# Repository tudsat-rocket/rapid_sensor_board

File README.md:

# Rapid Sensor Board
this module is meant to be a general-purpose amplifier which is going to be used for all analogue sensors which will be in the rocket, those include the WIKA pressure sensors as well as the fancy-fins strain gauges.

## Description
The main function of the module is to amplify signals with low voltage levels that are too small to be useful for our ADCs. Therefore the board has two sides with solder pads, one to connect to the IO board and one to connect to a sensor. The layout is designed in a way, that the sensor side is compatible with the WIKA TPR-Flex PCBs.

## Features
* Selectable gain (1-1000) -> the selection of RG1 will determine the gain (G = 1 + 49,4kOhm/RG)
* selectable offset -> output offset can either be 0V or Vcc/2
* Breakaway mounting holes
## Connections
### To IO-Board:
Connects the amplifier module with the IO-Board with the following pins:
* u+  ->  positive supply voltage (3-36V)
* u-  ->  gnd as "neg" supply voltage (only use in single supply mode) | reference for the output signal.
* o+  ->  amplified signal, references gnd (u-)
* ref  ->  selected reference signal (0V or Vcc/2) can be used to get additional information (e.g. detect noise on supply line(?))

### To sensor:
Connects the amplifier module with the Sensor with the following pins:
* u+  -> positive supply voltage (filtered supply voltage)
* u-  -> neg. supply voltage (gnd)
* s+  -> positive signal
* s-  -> negative signal

## User guideline:
The Gain resistor (RG1) must be chosen in a way that the expected maximum amplified voltage is lower than 4.85V (5V - 0.15V) and the expected minimum amplified voltage is higher than 0.1V if a smaller (or negative) output voltage is expected the solder jumper for the reference voltage needs to be connected to 3 to set an output shift.
Only if the connected sensor is expected to output a signal which exclusively results in an output signal that is in the above given values, can the reference solder jumper be set to 1.

The above-given adjustments are necessary as the IO module is only able to read values between 0V and 5V. A higher Input voltage can be used if the connected sensor needs a supply voltage which exceeds 5V. The amplified signal then still needs to be smaller than the given 4.85V.

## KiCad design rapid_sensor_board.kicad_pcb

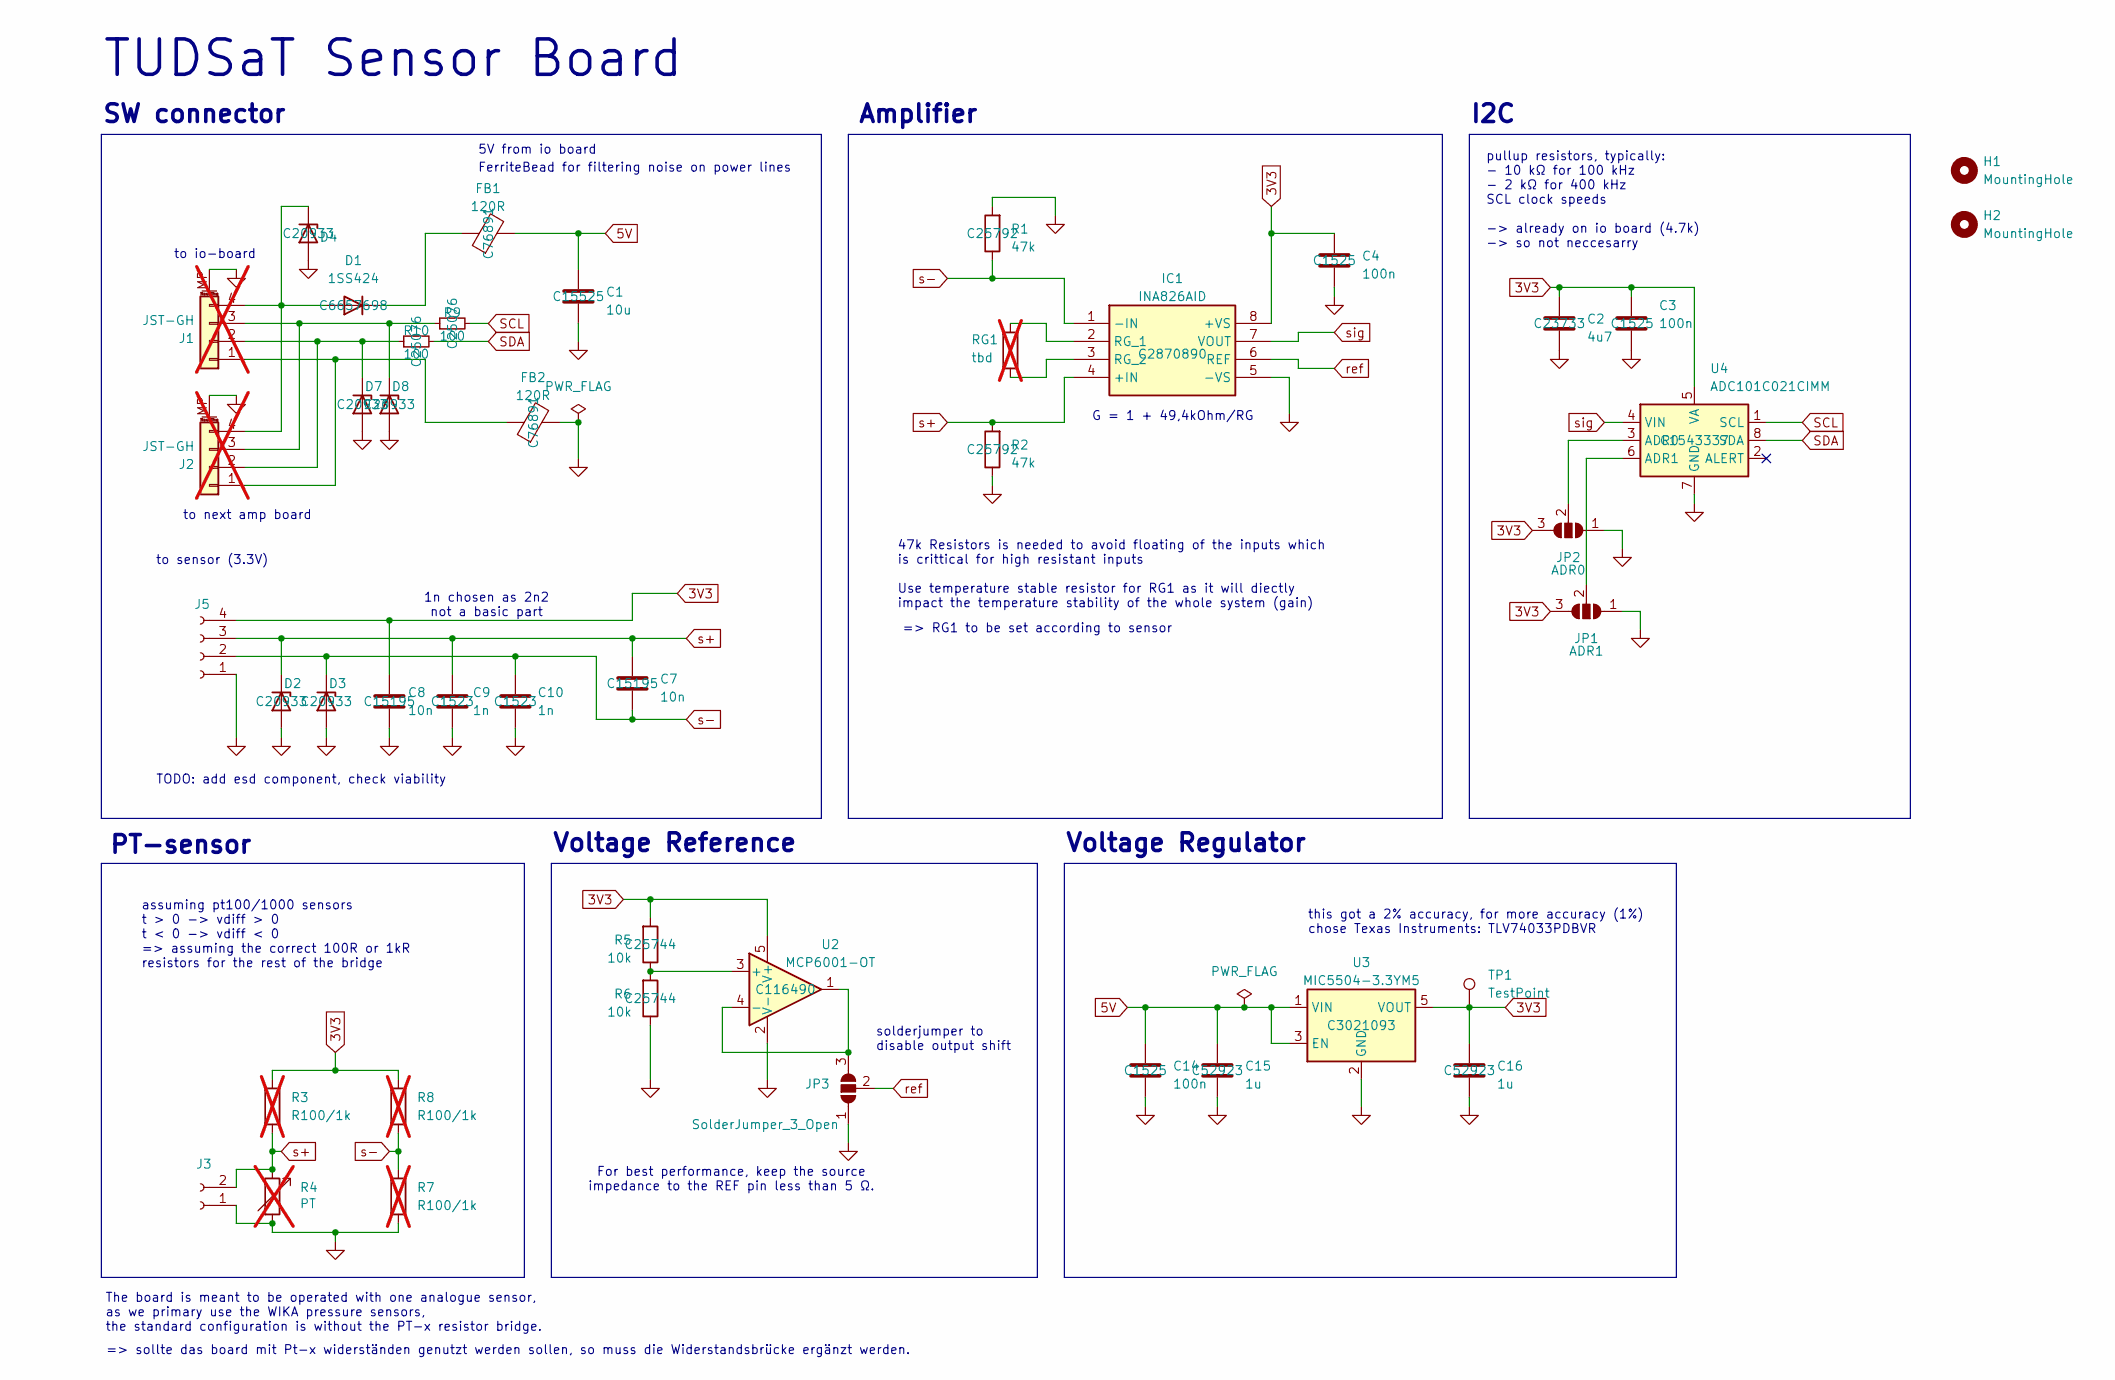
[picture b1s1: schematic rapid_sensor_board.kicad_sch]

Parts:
C1: 10u; C_0402_1005Metric; LCSC C15525
C2: 4u7; C_0402_1005Metric; LCSC C23733
C3, C4, C14: 100n; C_0402_1005Metric; LCSC C1525
C7, C8: 10n; C_0402_1005Metric; LCSC C15195
C9, C10: 1n; C_0402_1005Metric; LCSC C1523
C15, C16: 1u; C_0402_1005Metric; LCSC C52923
D1: 1SS424; D_SOD-523; LCSC C6657698
D2, D3, D7, D8: ESD5Z36; D_SOD-523; LCSC C20933
D4: ESD5Zxx; D_SOD-523; LCSC C20933
FB1, FB2: 120R; L_0402_1005Metric; LCSC C76891
H1, H2: MountingHole; MountingHole_2.2mm_M2_DIN965_Pad
IC1: INA826AID; WSON-8-1EP_3x3mm_P0.5mm_EP1.2x2mm; Mouser Part Number 595-INA826AID
J1, J2: JST-GH; JST_GH_SM04B-GHS-TB_1x04-1MP_P1.25mm_Horizontal; Part# BM04B-GHS-TBT; LCSC C161692; not fitted
J3: Conn_01x02_Socket; R_Axial_DIN0204_L3.6mm_D1.6mm_P1.90mm_Vertical
J5: Conn_01x04_Socket; PinHeader_1x04_P1.27mm_Vertical
JP1: ADR1; SolderJumper-3_P1.3mm_Open_RoundedPad1.0x1.5mm
JP2: ADR0; SolderJumper-3_P1.3mm_Open_RoundedPad1.0x1.5mm
JP3: SolderJumper_3_Open; SolderJumper-3_P1.3mm_Open_Pad1.0x1.5mm
R1: 47k; R_0402_1005Metric; LCSC C25792
R2: 47k; R_0402_1005Metric_Pad0.72x0.64mm_HandSolder; LCSC C25792
R3, R7, R8: R100/1k; R_0805_2012Metric_Pad1.20x1.40mm_HandSolder; not fitted
R4: PT; not fitted
R5, R6: 10k; R_0402_1005Metric_Pad0.72x0.64mm_HandSolder; LCSC C25744
R9, R10: 100; R_0402_1005Metric; LCSC C25076
RG1: tbd; R_1206_3216Metric_Pad1.30x1.75mm_HandSolder; not fitted
TP1: TestPoint; TestPoint_Pad_D1.5mm
U2: MCP6001-OT; SOT-23-5; LCSC C116490
U3: MIC5504-3.3YM5; SOT-23-5; LCSC C3021093
U4: ADC101C021CIMM; VSSOP-8_3x3mm_P0.65mm; LCSC C1543337

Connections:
3V3: C2.1, C3.1, C4.1, C8.1, C16.1, IC1.8 (+VS), J5.4, JP1.3 (B), JP2.3 (B), R3.1, R5.2, R8.1, TP1.1, U2.5 (V+), U3.5 (VOUT), U4.5 (VA)
5V: C1.1, C14.1, C15.1, FB1.2, U3.1 (VIN), U3.3 (EN)
GND: C1.2, C2.2, C3.2, C4.2, C8.2, C9.2, C10.2, C14.2, C15.2, C16.2, D2.2 (A), D3.2 (A), D4.2 (A), D7.2 (A), D8.2 (A), FB2.2, IC1.5 (-VS), J1.MP (MountPin), J2.MP (MountPin), J3.1, J5.1, JP1.1 (A), JP2.1 (A), JP3.1 (A), R1.2, R2.1, R4.2, R6.1, R7.2, U2.2 (V-), U3.2 (GND), U4.7 (GND)
unnamed: D1.2 (A), D4.1 (K), J1.4, J2.4
unnamed: D1.1 (K), FB1.1
unnamed: D7.1 (K), J1.2, J2.2, R10.1
unnamed: D8.1 (K), J1.3, J2.3, R9.1
unnamed: IC1.2 (RG_1), RG1.2
unnamed: IC1.3 (RG_2), RG1.1
unnamed: FB2.1, J1.1, J2.1
unnamed: JP1.2 (C), U4.6 (ADR1)
unnamed: JP2.2 (C), U4.3 (ADR0)
unnamed: JP3.3 (B), U2.1, U2.4 (-)
unnamed: R5.1, R6.2, U2.3 (+)
SCL: R9.2, U4.1 (SCL)
SDA: R10.2, U4.8 (SDA)
ref: IC1.6 (REF), JP3.2 (C)
s+: C7.1, C9.1, D2.1 (K), IC1.4 (+IN), J3.2, J5.3, R2.2, R3.2, R4.1
s-: C7.2, C10.1, D3.1 (K), IC1.1 (-IN), J5.2, R1.1, R7.1, R8.2
sig: IC1.7 (VOUT), U4.4 (VIN)

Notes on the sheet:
pullup resistors, typically: - 10 kΩ for 100 kHz - 2 kΩ for 400 kHz SCL clock speeds -> already on io board (4.7k) -> so not neccesarry
to sensor (3.3V)
G = 1 + 49,4kOhm/RG
SW connector
Voltage Regulator
to next amp board
The board is meant to be operated with one analogue sensor, as we primary use the WIKA pressure sensors, the standard configuration is without the PT-x resistor bridge.
=> sollte das board mit Pt-x widerständen genutzt werden sollen, so muss die Widerstandsbrücke ergänzt werden.
TODO: add esd component, check viability
5V from io board
FerriteBead for filtering noise on power lines
solderjumper to disable output shift
1n chosen as 2n2 not a basic part
TUDSaT Sensor Board
Voltage Reference
47k Resistors is needed to avoid floating of the inputs which is crittical for high resistant inputs Use temperature stable resistor for RG1 as it will diectly impact the temperature stability of the whole system (gain)
I2C
assuming pt100/1000 sensors t > 0 -> vdiff > 0 t < 0 -> vdiff < 0 => assuming the correct 100R or 1kR resistors for the rest of the bridge
Amplifier
PT-sensor
this got a 2% accuracy, for more accuracy (1%) chose Texas Instruments: TLV74033PDBVR
to io-board
For best performance, keep the source impedance to the REF pin less than 5 Ω.
=> RG1 to be set according to sensor

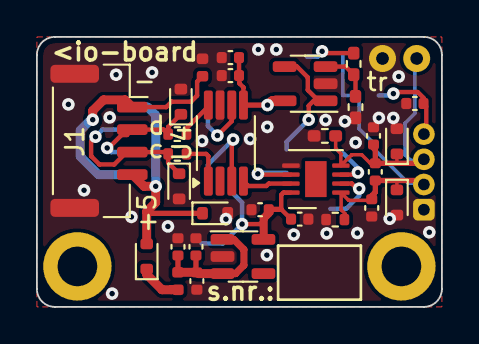
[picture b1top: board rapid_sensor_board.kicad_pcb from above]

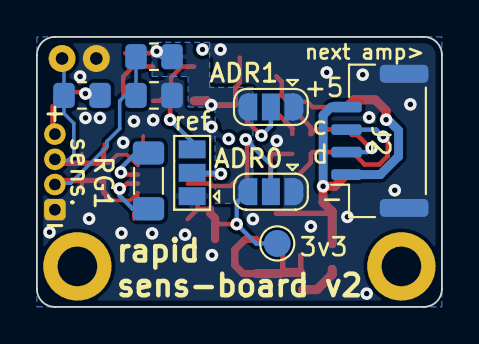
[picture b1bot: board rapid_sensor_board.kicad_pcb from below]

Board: 4 copper layers, 22.5 x 15.0 mm, 43 parts (9 on the bottom side), 20 nets.

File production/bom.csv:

Designator,Footprint,Quantity,Value,LCSC Part #
C1,0402,1,10u,C15525
"C10, C9",0402,2,1n,C1523
"C14, C3, C4",0402,3,100n,C1525
"C15, C16",0402,2,1u,C52923
C2,0402,1,4u7,C23733
"C7, C8",0402,2,10n,C15195
D1,D_SOD-523,1,1SS424,C6657698
"D2, D3, D7, D8",D_SOD-523,4,ESD5Z36,C20933
D4,D_SOD-523,1,ESD5Zxx,C20933
"FB1, FB2",0402,2,120R,C76891
IC1,WSON-8-1EP_3x3mm_P0.5mm_EP1.2x2mm,1,INA826AID,C2870890
J3,R_Axial_DIN0204_L3.6mm_D1.6mm_P1.90mm_Vertical,1,Conn_01x02_Socket,
J5,PinHeader_1x04_P1.27mm_Vertical,1,Conn_01x04_Socket,
JP1,SolderJumper-3_P1.3mm_Open_RoundedPad1.0x1.5mm,1,ADR1,
JP2,SolderJumper-3_P1.3mm_Open_RoundedPad1.0x1.5mm,1,ADR0,
JP3,SolderJumper-3_P1.3mm_Open_Pad1.0x1.5mm,1,SolderJumper_3_Open,
"R1, R2",0402,2,47k,C25792
"R10, R9",0402,2,100,C25076
"R5, R6",0402,2,10k,C25744
TP1,TestPoint_Pad_D1.5mm,1,TestPoint,
U2,SOT-23-5,1,MCP6001-OT,C116490
U3,SOT-23-5,1,MIC5504-3.3YM5,C3021093
U4,VSSOP-8_3x3mm_P0.65mm,1,ADC101C021CIMM,C1543337

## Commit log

2026-03-26 added lcsc numbers
2026-03-26 Rename module to Rapid Sensor Board
    Updated the module name and clarified its purpose.
2026-04-29 some changes, added production files
2026-05-04 added scematic as pdf
